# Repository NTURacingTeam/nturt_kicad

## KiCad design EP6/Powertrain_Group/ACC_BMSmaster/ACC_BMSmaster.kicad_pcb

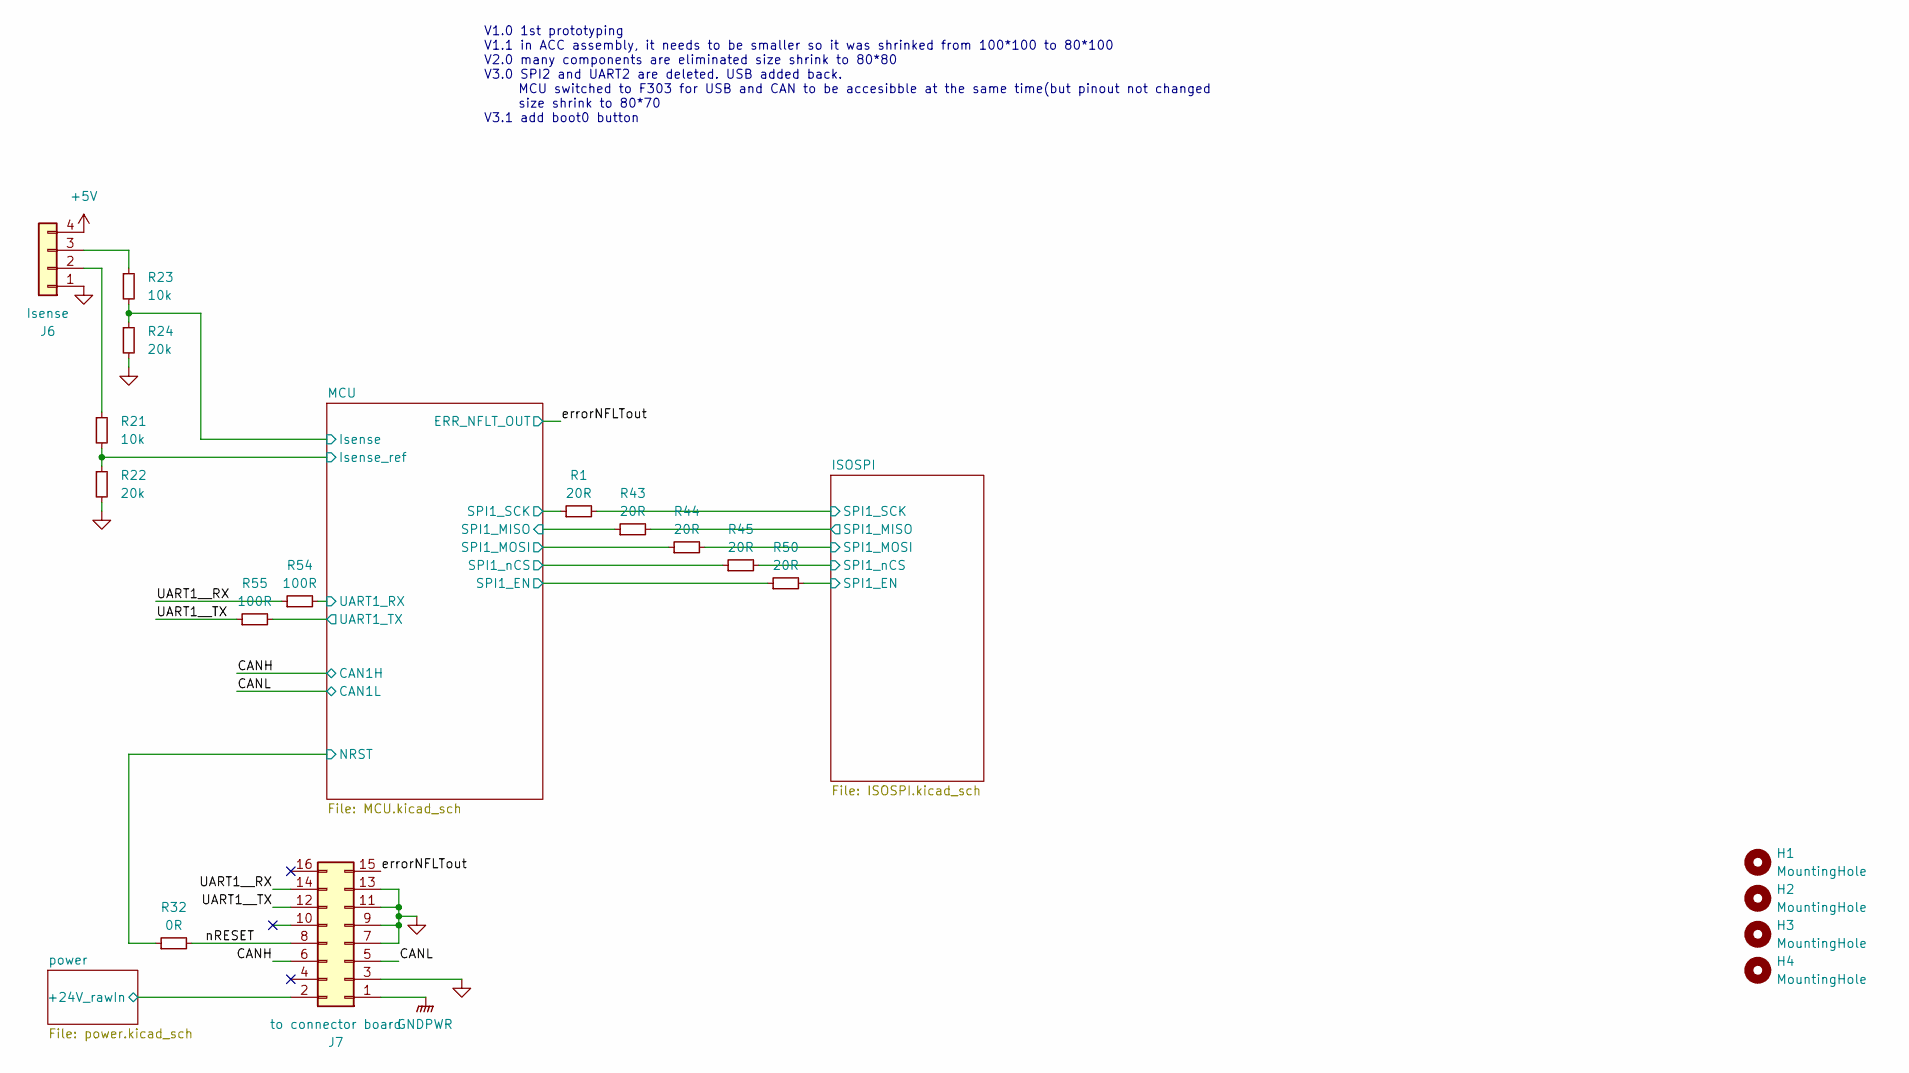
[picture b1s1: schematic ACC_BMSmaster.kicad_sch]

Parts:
H1, H2, H3, H4: MountingHole; MountingHole_3.2mm_M3
J6: Isense; JST_PH_B4B-PH-K_1x04_P2.00mm_Vertical
J7: to connector board; IDC-Header_2x08_P2.54mm_Vertical
R1, R43, R44, R45, R50: 20R; R_0402_1005Metric
R21, R23: 10k; R_0402_1005Metric
R22, R24: 20k; R_0402_1005Metric
R32: 0R; R_0402_1005Metric
R54, R55: 100R; R_0402_1005Metric

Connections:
+5V: J6.4; also elsewhere on the board
/CANH: J7.6; also elsewhere on the board
/CANL: J7.5; also elsewhere on the board
/ISOSPI/SPI1_EN: R50.2; also elsewhere on the board
/ISOSPI/SPI1_MISO: R43.2; also elsewhere on the board
/ISOSPI/SPI1_MOSI: R44.2; also elsewhere on the board
/ISOSPI/SPI1_SCK: R1.2; also elsewhere on the board
/ISOSPI/SPI1_nCS: R45.2; also elsewhere on the board
/MCU/Isense: R23.2, R24.1; also elsewhere on the board
/MCU/Isense_ref: R21.2, R22.1; also elsewhere on the board
/MCU/SPI1_EN: R50.1; also elsewhere on the board
/MCU/SPI1_MISO: R43.1; also elsewhere on the board
/MCU/SPI1_MOSI: R44.1; also elsewhere on the board
/MCU/SPI1_SCK: R1.1; also elsewhere on the board
/MCU/SPI1_nCS: R45.1; also elsewhere on the board
/MCU/SWD_NRST: R32.1; also elsewhere on the board
/MCU/UART1_RX: R54.2; also elsewhere on the board
/MCU/UART1_TX: R55.2; also elsewhere on the board
/UART1__RX: J7.14, R54.1
/UART1__TX: J7.12, R55.1
/errorNFLTout: J7.15; also elsewhere on the board
/nRESET: J7.8, R32.2
/power/+24V_preCMfilter: J7.2; also elsewhere on the board
GND: J6.1, J7.3, J7.7, J7.9, J7.11, J7.13, R22.2, R24.2; also elsewhere on the board
GNDPWR: J7.1; also elsewhere on the board
unnamed: J6.2, R21.1
unnamed: J6.3, R23.1

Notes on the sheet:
V1.0 1st prototyping V1.1 in ACC assembly, it needs to be smaller so it was shrinked from 100*100 to 80*100 V2.0 many components are eliminated size shrink to 80*80 V3.0 SPI2 and UART2 are deleted. USB added back. MCU switched to F303 for USB and CAN to be accesibble at the same time(but pinout not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

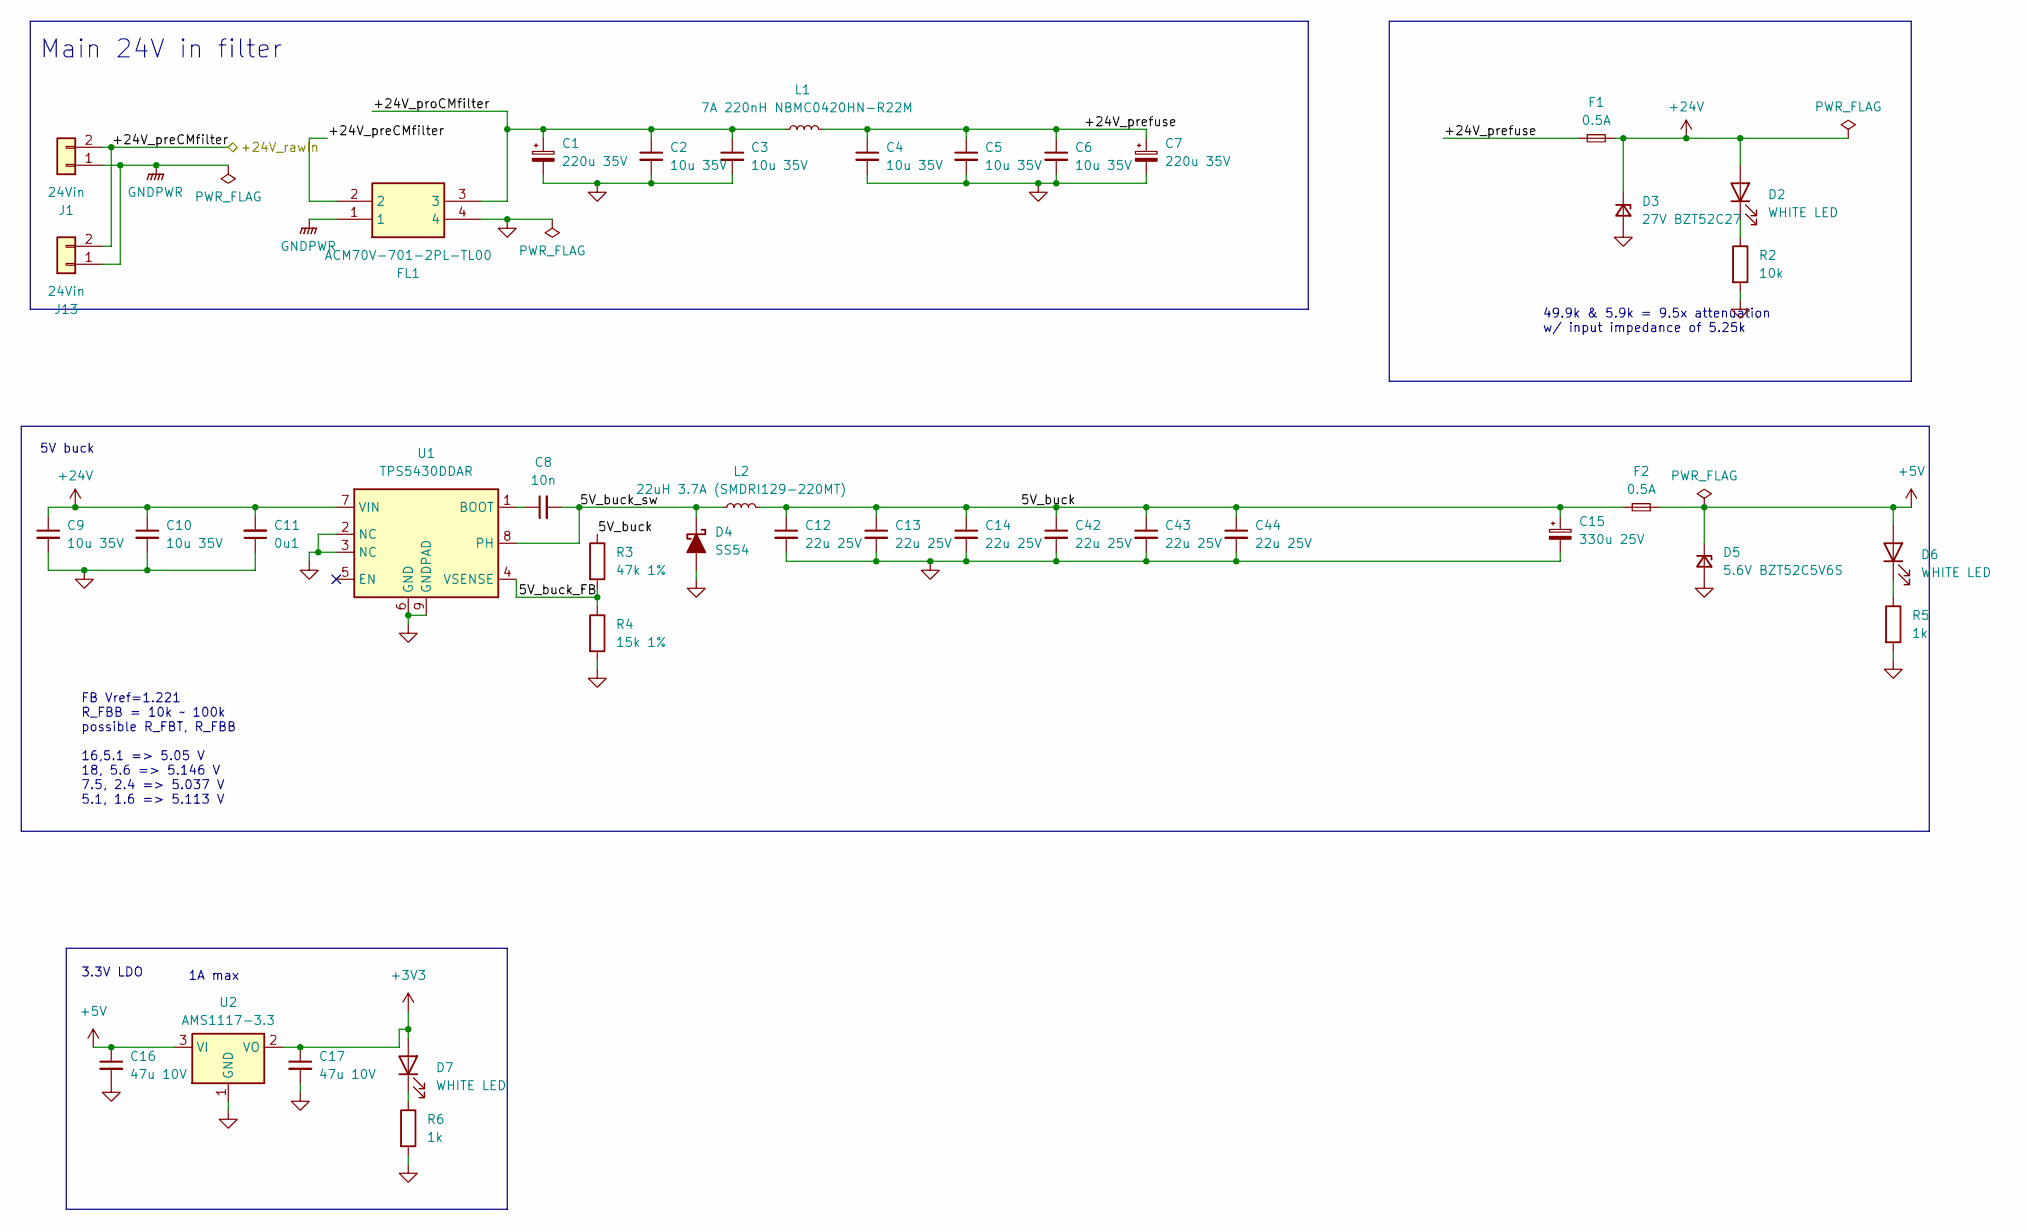
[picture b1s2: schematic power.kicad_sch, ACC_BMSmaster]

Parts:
C1, C7: 220u 35V; CP_Radial_D8.0mm_P3.80mm
C2, C3, C4, C5, C6, C9, C10: 10u 35V; C_1206_3216Metric
C8: 10n; C_0603_1608Metric
C11: 0u1; C_0603_1608Metric
C12, C13, C14, C42, C43, C44: 22u 25V; C_1206_3216Metric
C15: 330u 25V; CP_Radial_D8.0mm_P3.80mm
C16, C17: 47u 10V; C_1206_3216Metric
D2, D6, D7: WHITE LED; LED_0603_1608Metric
D3: 27V BZT52C27; D_SOD-323
D4: SS54; D_SMA
D5: 5.6V BZT52C5V6S; D_SOD-323
F1, F2: 0.5A; Fuse_1206_3216Metric
FL1: ACM70V-701-2PL-TL00; ACM70V7012PLTL00; Mouser Part Number 810-ACM70V7012PLTL00
J1, J13: 24Vin; JST_VH_B2P-VH_1x02_P3.96mm_Vertical
L1: 7A 220nH NBMC0420HN-R22M; L_Ferrocore_DLG-0403
L2: 22uH 3.7A (SMDRI129-220MT); L_Bourns_SRR1260
R2: 10k; R_0402_1005Metric
R3: 47k 1%; R_0603_1608Metric
R4: 15k 1%; R_0603_1608Metric
R5, R6: 1k; R_0402_1005Metric
U1: TPS5430DDAR; TI_SO-PowerPAD-8_ThermalVias
U2: AMS1117-3.3; SOT-223-3_TabPin2

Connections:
+3V3: C17.1, D7.2 (A), U2.2 (VO); also elsewhere on the board
+5V: C16.1, D5.1 (K), D6.2 (A), F2.2, U2.3 (VI); also elsewhere on the board
+24V: C9.1, C10.1, C11.2, D2.2 (A), D3.1 (K), F1.2, U1.7 (VIN)
/power/5V_buck: C12.1, C13.1, C14.1, C15.1, C42.1, C43.1, C44.1, F2.1, L2.2, R3.1
/power/5V_buck_FB: R3.2, R4.1, U1.4 (VSENSE)
/power/5V_buck_sw: C8.2, D4.1 (K), L2.1, U1.8 (PH)
/power/+24V_preCMfilter: FL1.2, J1.2, J13.2; also elsewhere on the board
/power/+24V_prefuse: C4.1, C5.1, C6.1, C7.1, F1.1, L1.2
/power/+24V_proCMfilter: C1.1, C2.1, C3.1, FL1.3, L1.1
GND: C1.2, C2.2, C3.2, C4.2, C5.2, C6.2, C7.2, C9.2, C10.2, C11.1, C12.2, C13.2, C14.2, C15.2, C16.2, C17.2, C42.2, C43.2, C44.2, D3.2 (A), D4.2 (A), D5.2 (A), FL1.4, R2.2, R4.2, R5.2, R6.2, U1.2 (NC), U1.3 (NC), U1.6 (GND), U1.9 (GNDPAD), U2.1 (GND); also elsewhere on the board
GNDPWR: FL1.1, J1.1, J13.1; also elsewhere on the board
unnamed: D2.1 (K), R2.1
unnamed: D6.1 (K), R5.1
unnamed: D7.1 (K), R6.1
unnamed: C8.1, U1.1 (BOOT)

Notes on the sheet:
49.9k & 5.9k = 9.5x attenuation w/ input impedance of 5.25k
FB Vref=1.221 R_FBB = 10k ~ 100k possible R_FBT, R_FBB 16,5.1 => 5.05 V 18, 5.6 => 5.146 V 7.5, 2.4 => 5.037 V 5.1, 1.6 => 5.113 V
1A max
5V buck
3.3V LDO
Main 24V in filter

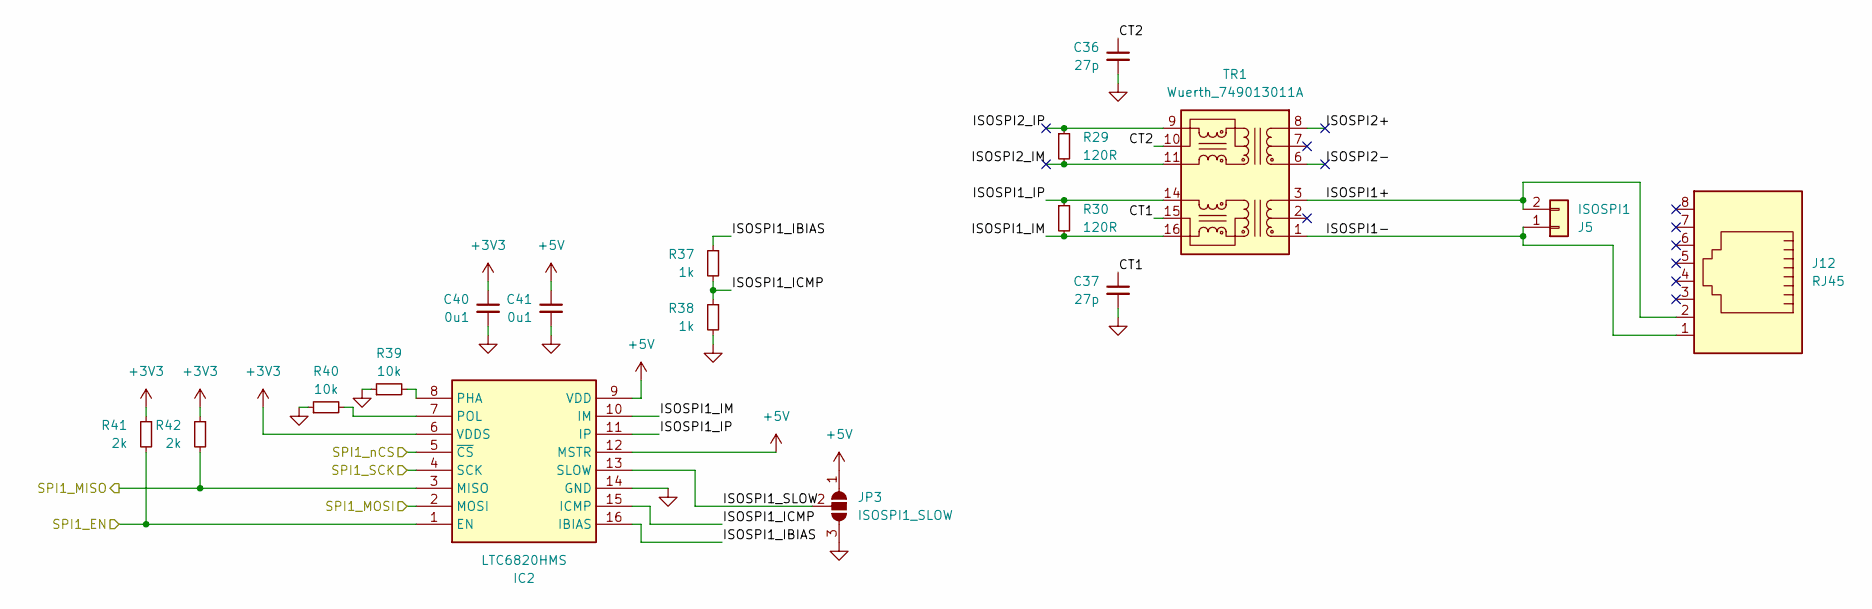
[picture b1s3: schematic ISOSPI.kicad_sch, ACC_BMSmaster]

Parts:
C36, C37: 27p; C_0402_1005Metric
C40, C41: 0u1; C_0402_1005Metric
IC2: LTC6820HMS; SOP50P490X110-16N; Mouser Part Number 584-LTC6820HMS#PBF
J5: ISOSPI1; JST_XH_B2B-XH-A_1x02_P2.50mm_Vertical
J12: RJ45; RJ45_Amphenol_54602-x08_Horizontal
JP3: ISOSPI1_SLOW; SolderJumper-3_P1.3mm_Open_RoundedPad1.0x1.5mm
R29, R30: 120R; R_0402_1005Metric
R37, R38: 1k; R_0402_1005Metric
R39, R40: 10k; R_0402_1005Metric
R41, R42: 2k; R_0402_1005Metric
TR1: Wuerth_749013011A; Transformer_Ethernet_Wuerth_749013011A

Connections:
+3V3: C40.1, IC2.6 (VDDS), R41.1, R42.1; also elsewhere on the board
+5V: C41.1, IC2.9 (VDD), IC2.12 (MSTR), JP3.1 (A); also elsewhere on the board
/ISOSPI/CT1: C37.1, TR1.15 (C_TX)
/ISOSPI/CT2: C36.1, TR1.10 (C_RX)
/ISOSPI/ISOSPI1+: J5.2, J12.2, TR1.3 (TD-)
/ISOSPI/ISOSPI1-: J5.1, J12.1, TR1.1 (TD+)
/ISOSPI/ISOSPI1_IBIAS: IC2.16 (IBIAS), R37.1
/ISOSPI/ISOSPI1_ICMP: IC2.15 (ICMP), R37.2, R38.1
/ISOSPI/ISOSPI1_IM: IC2.10 (IM), R30.2, TR1.16 (TX+)
/ISOSPI/ISOSPI1_IP: IC2.11 (IP), R30.1, TR1.14 (TX-)
/ISOSPI/ISOSPI1_SLOW: IC2.13 (SLOW), JP3.2 (C)
/ISOSPI/ISOSPI2+: TR1.8 (RD-)
/ISOSPI/ISOSPI2-: TR1.6 (RD+)
/ISOSPI/ISOSPI2_IM: R29.2, TR1.11 (RX+)
/ISOSPI/ISOSPI2_IP: R29.1, TR1.9 (RX-)
/ISOSPI/SPI1_EN: IC2.1 (EN), R41.2; also elsewhere on the board
/ISOSPI/SPI1_MISO: IC2.3 (MISO), R42.2; also elsewhere on the board
/ISOSPI/SPI1_MOSI: IC2.2 (MOSI); also elsewhere on the board
/ISOSPI/SPI1_SCK: IC2.4 (SCK); also elsewhere on the board
/ISOSPI/SPI1_nCS: IC2.5 (~CS); also elsewhere on the board
GND: C36.2, C37.2, C40.2, C41.2, IC2.14 (GND), JP3.3 (B), R38.2, R39.1, R40.1; also elsewhere on the board
unnamed: IC2.8 (PHA), R39.2
unnamed: IC2.7 (POL), R40.2

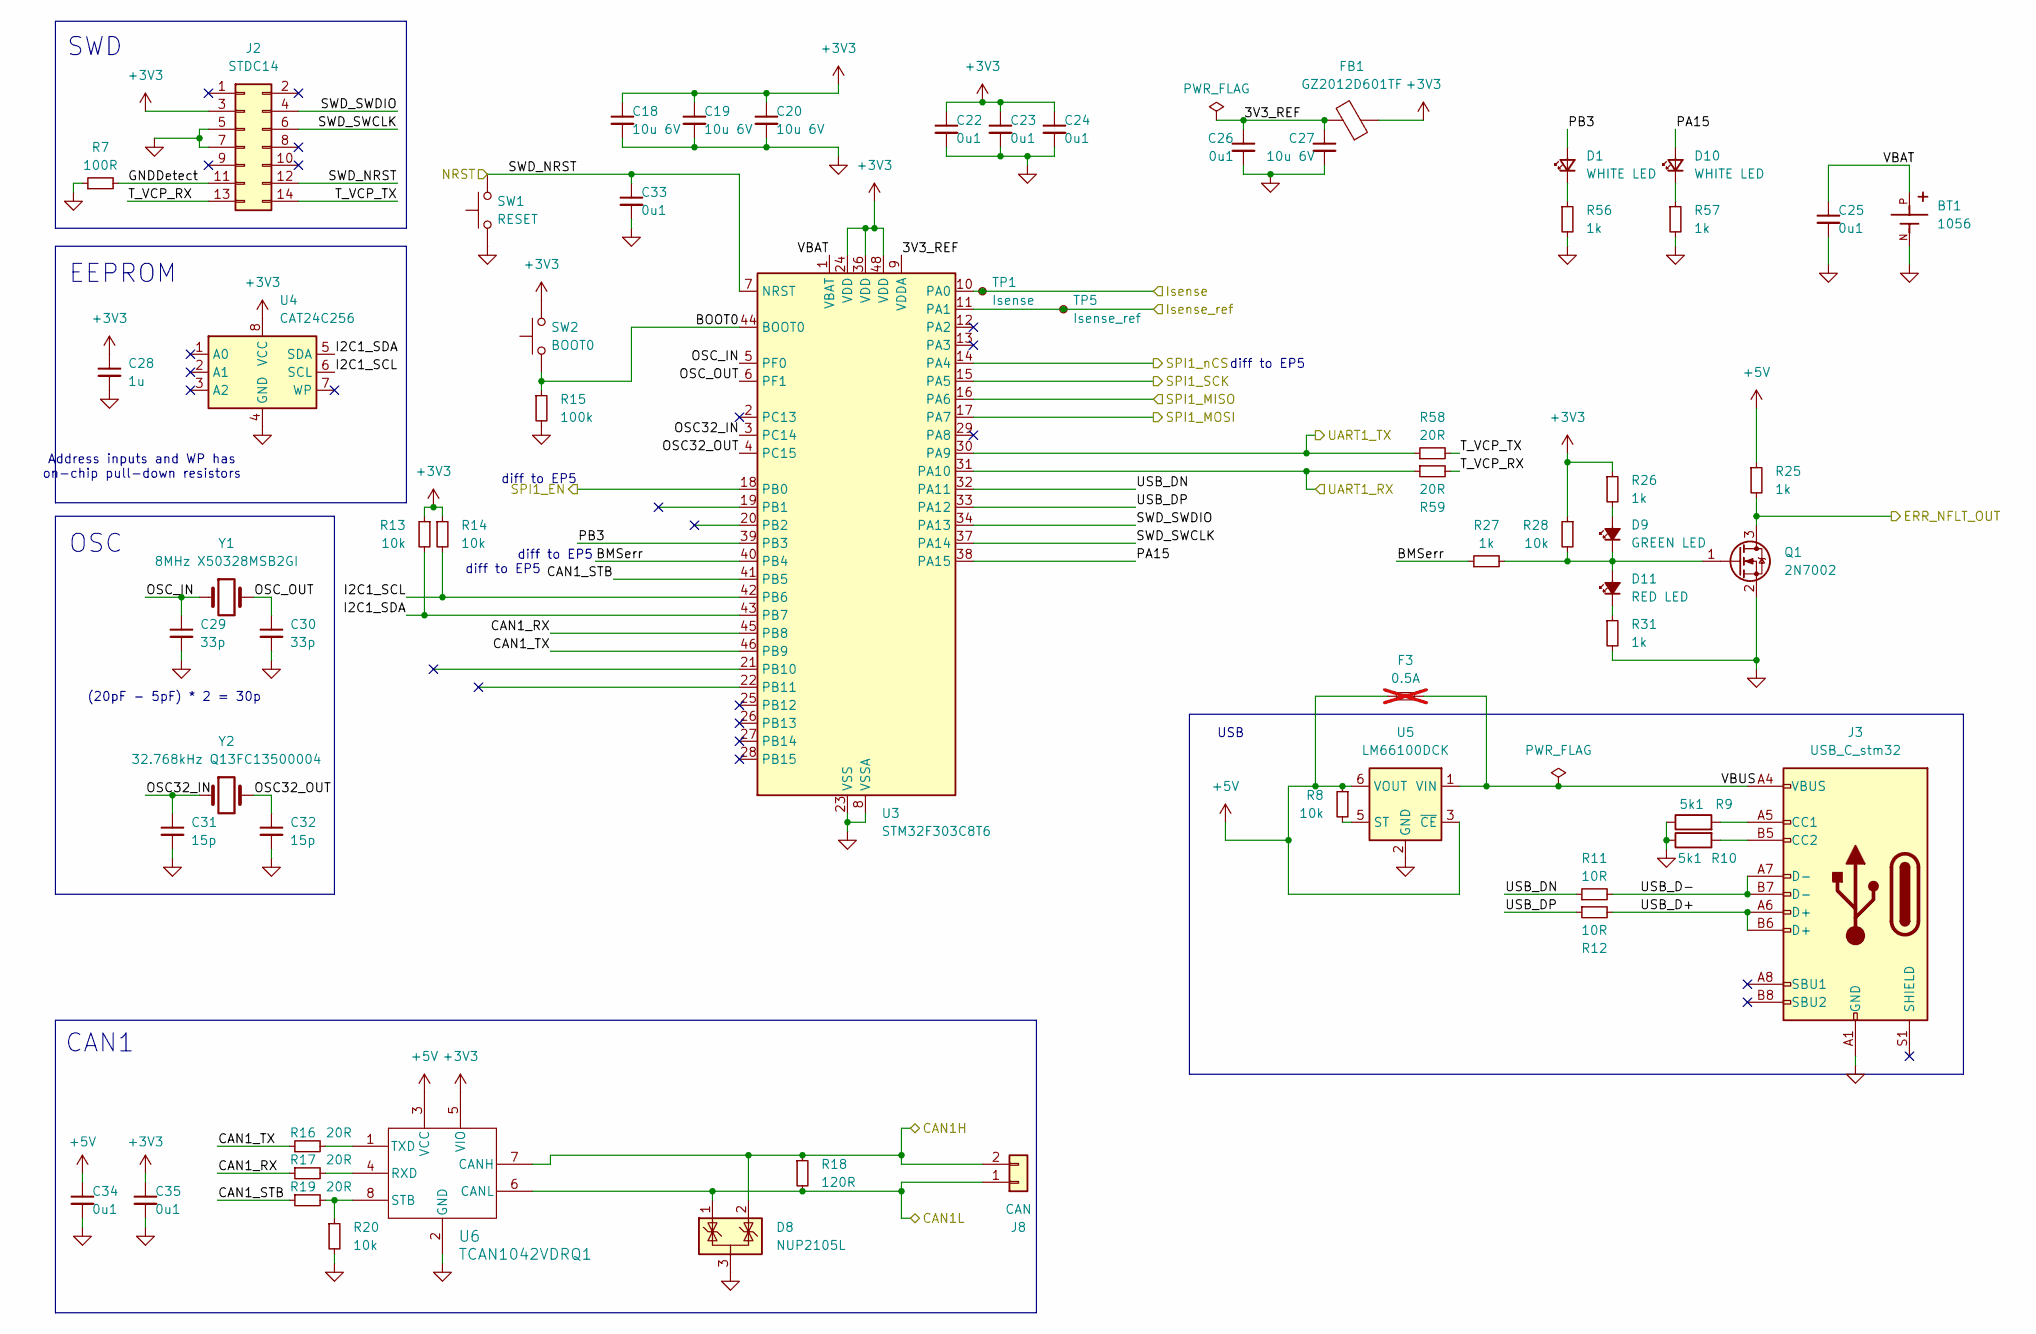
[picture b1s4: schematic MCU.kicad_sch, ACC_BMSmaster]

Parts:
BT1: 1056; BAT_1056; PARTREV D
C18, C19, C20, C27: 10u 6V; C_0402_1005Metric
C22, C23, C24, C25, C26, C33, C34, C35: 0u1; C_0402_1005Metric
C28: 1u; C_0402_1005Metric
C29, C30: 33p; C_0402_1005Metric
C31, C32: 15p; C_0402_1005Metric
D1, D10: WHITE LED; LED_0603_1608Metric
D8: NUP2105L; SOT-23
D9: GREEN LED; LED_0603_1608Metric
D11: RED LED; LED_0603_1608Metric
F3: 0.5A; Fuse_1206_3216Metric; not fitted
FB1: GZ2012D601TF; L_0805_2012Metric
J2: STDC14; box_header_14P_pitch127
J3: USB_C_stm32; USB_C_Receptacle_GCT_USB4105-xx-A_16P_TopMnt_Horizontal
J8: CAN; JST_XH_B2B-XH-A_1x02_P2.50mm_Vertical
Q1: 2N7002; SOT-23
R7: 100R; R_0402_1005Metric
R8, R13, R14, R20, R28: 10k; R_0402_1005Metric
R9, R10: 5k1; R_0402_1005Metric
R11, R12: 10R; R_0402_1005Metric
R15: 100k; R_0402_1005Metric
R16, R17, R19, R58, R59: 20R; R_0402_1005Metric
R18: 120R; R_0402_1005Metric
R25, R26, R27, R31, R56, R57: 1k; R_0402_1005Metric
SW1: RESET; SW_Tactile_SPST_NO_Straight_CK_PTS636Sx25SMTRLFS
SW2: BOOT0; SW_Tactile_SPST_NO_Straight_CK_PTS636Sx25SMTRLFS
TP1: Isense; TestPoint_Pad_D1.0mm
TP5: Isense_ref; TestPoint_Pad_D1.0mm
U3: STM32F303C8T6; LQFP-48_7x7mm_P0.5mm
U4: CAT24C256; SOIC-8_3.9x4.9mm_P1.27mm
U5: LM66100DCK; SOT-363_SC-70-6
U6: TCAN1042VDRQ1; SOIC-8_3.9x4.9mm_P1.27mm
Y1: 8MHz X50328MSB2GI; Crystal_SMD_5032-2Pin_5.0x3.2mm
Y2: 32.768kHz Q13FC13500004; Crystal_SMD_3215-2Pin_3.2x1.5mm

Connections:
+3V3: C18.1, C19.1, C20.1, C22.1, C23.1, C24.1, C28.1, C35.1, FB1.1, J2.3, R13.1, R14.1, R26.1, R28.1, SW2.2, U3.24 (VDD), U3.36 (VDD), U3.48 (VDD), U4.8 (VCC), U6.5 (VIO); also elsewhere on the board
+5V: C34.1, F3.1, R8.1, R25.1, U5.3 (~CE), U5.6 (VOUT), U6.3 (VCC); also elsewhere on the board
/CANH: D8.2 (K), J8.2, R18.1, U6.7 (CANH); also elsewhere on the board
/CANL: D8.1 (K), J8.1, R18.2, U6.6 (CANL); also elsewhere on the board
/MCU/3V3_REF: C26.1, C27.1, FB1.2, U3.9 (VDDA)
/MCU/BMSerr: R27.1, U3.40 (PB4)
/MCU/BOOT0: R15.1, SW2.1, U3.44 (BOOT0)
/MCU/CAN1_RX: R17.1, U3.45 (PB8)
/MCU/CAN1_STB: R19.1, U3.41 (PB5)
/MCU/CAN1_TX: R16.1, U3.46 (PB9)
/MCU/GNDDetect: J2.11, R7.2
/MCU/I2C1_SCL: R14.2, U3.42 (PB6), U4.6 (SCL)
/MCU/I2C1_SDA: R13.2, U3.43 (PB7), U4.5 (SDA)
/MCU/Isense: TP1.1, U3.10 (PA0); also elsewhere on the board
/MCU/Isense_ref: TP5.1, U3.11 (PA1); also elsewhere on the board
/MCU/OSC32_IN: C31.1, U3.3 (PC14), Y2.1
/MCU/OSC32_OUT: C32.1, U3.4 (PC15), Y2.2
/MCU/OSC_IN: C29.1, U3.5 (PF0), Y1.1
/MCU/OSC_OUT: C30.1, U3.6 (PF1), Y1.2
/MCU/PA15: D10.2 (A), U3.38 (PA15)
/MCU/PB3: D1.2 (A), U3.39 (PB3)
/MCU/SPI1_EN: U3.18 (PB0); also elsewhere on the board
/MCU/SPI1_MISO: U3.16 (PA6); also elsewhere on the board
/MCU/SPI1_MOSI: U3.17 (PA7); also elsewhere on the board
/MCU/SPI1_SCK: U3.15 (PA5); also elsewhere on the board
/MCU/SPI1_nCS: U3.14 (PA4); also elsewhere on the board
/MCU/SWD_NRST: C33.1, J2.12, SW1.2, U3.7 (NRST); also elsewhere on the board
/MCU/SWD_SWCLK: J2.6, U3.37 (PA14)
/MCU/SWD_SWDIO: J2.4, U3.34 (PA13)
/MCU/T_VCP_RX: J2.13, R59.2
/MCU/T_VCP_TX: J2.14, R58.2
/MCU/UART1_RX: R59.1, U3.31 (PA10); also elsewhere on the board
/MCU/UART1_TX: R58.1, U3.30 (PA9); also elsewhere on the board
/MCU/USB_D+: J3.A6 (D+), J3.B6 (D+), R12.2
/MCU/USB_D-: J3.A7 (D-), J3.B7 (D-), R11.2
/MCU/USB_DN: R11.1, U3.32 (PA11)
/MCU/USB_DP: R12.1, U3.33 (PA12)
/MCU/VBAT: BT1.P, C25.1, U3.1 (VBAT)
/MCU/VBUS: F3.2, J3.A4 (VBUS), J3.A9 (VBUS), J3.B4 (VBUS), J3.B9 (VBUS), U5.1 (VIN)
/errorNFLTout: Q1.3 (D), R25.2; also elsewhere on the board
GND: BT1.N, C18.2, C19.2, C20.2, C22.2, C23.2, C24.2, C25.2, C26.2, C27.2, C28.2, C29.2, C30.2, C31.2, C32.2, C33.2, C34.2, C35.2, D8.3 (A), J2.5, J2.7, J3.A1 (GND), J3.A12 (GND), J3.B1 (GND), J3.B12 (GND), Q1.2 (S), R7.1, R9.1, R10.1, R15.2, R20.2, R31.2, R56.2, R57.2, SW1.1, U3.8 (VSSA), U3.23 (VSS), U3.35 (VSS), U3.47 (VSS), U4.4 (GND), U5.2 (GND), U6.2 (GND); also elsewhere on the board
unnamed: D1.1 (K), R56.1
unnamed: D9.2 (A), R26.2
unnamed: D10.1 (K), R57.1
unnamed: D9.1 (K), D11.2 (A), Q1.1 (G), R27.2, R28.2
unnamed: D11.1 (K), R31.1
unnamed: J3.A5 (CC1), R9.2
unnamed: J3.B5 (CC2), R10.2
unnamed: R8.2, U5.5 (ST)
unnamed: R17.2, U6.4 (RXD)
unnamed: R19.2, R20.1, U6.8 (STB)
unnamed: R16.2, U6.1 (TXD)

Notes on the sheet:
diff to EP5
EEPROM
SWD
Address inputs and WP has on-chip pull-down resistors
OSC
(20pF - 5pF) * 2 = 30p
USB
CAN1

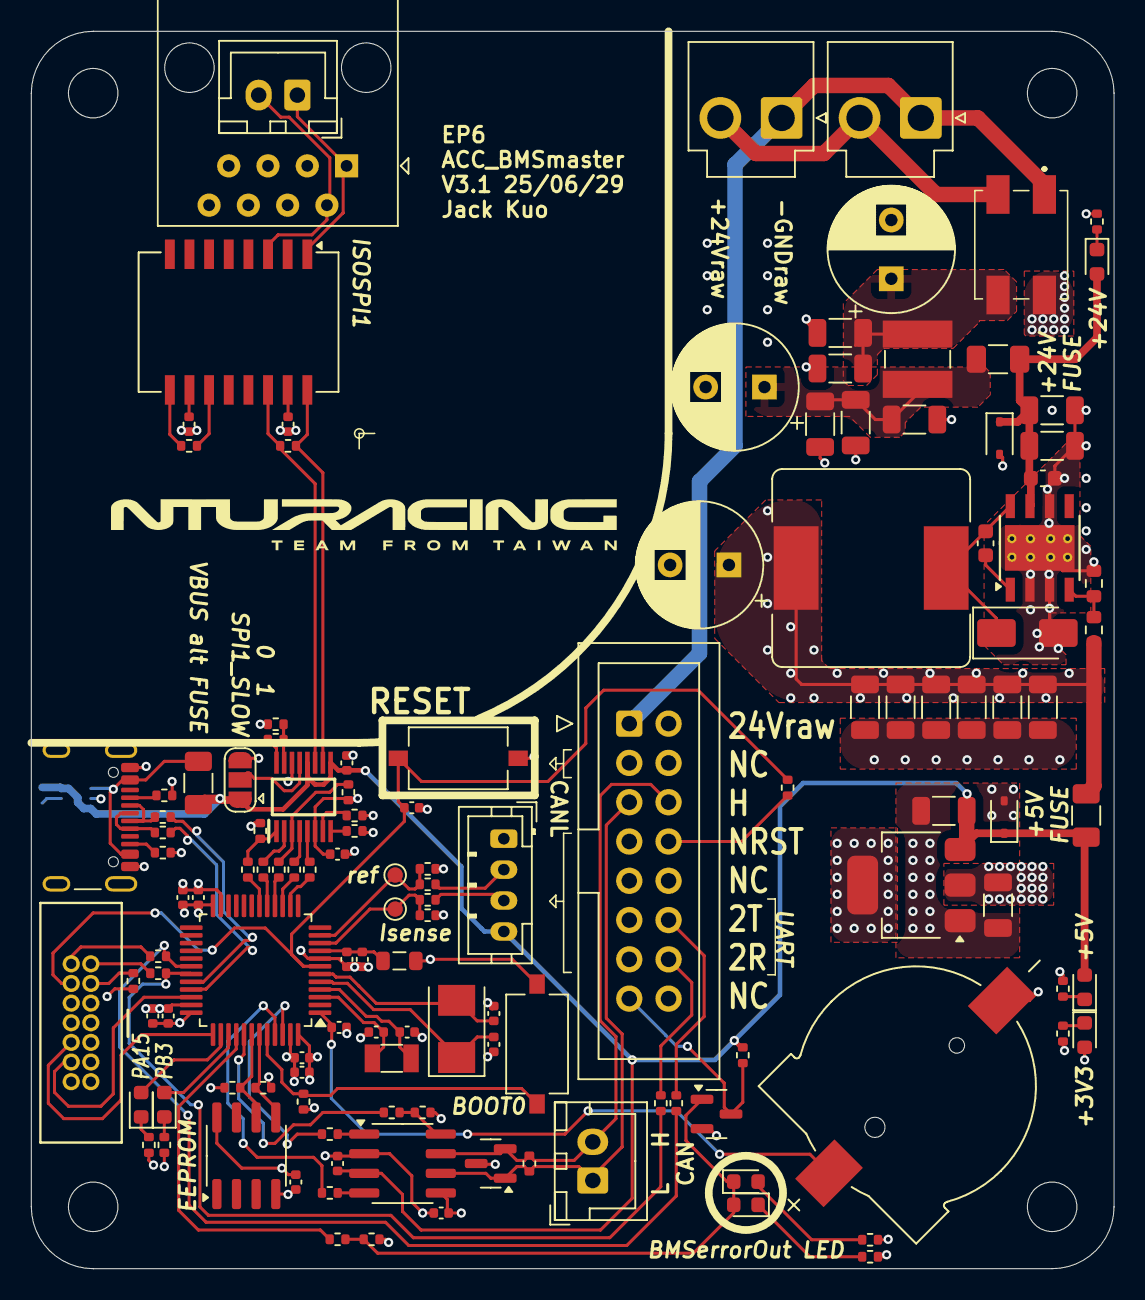
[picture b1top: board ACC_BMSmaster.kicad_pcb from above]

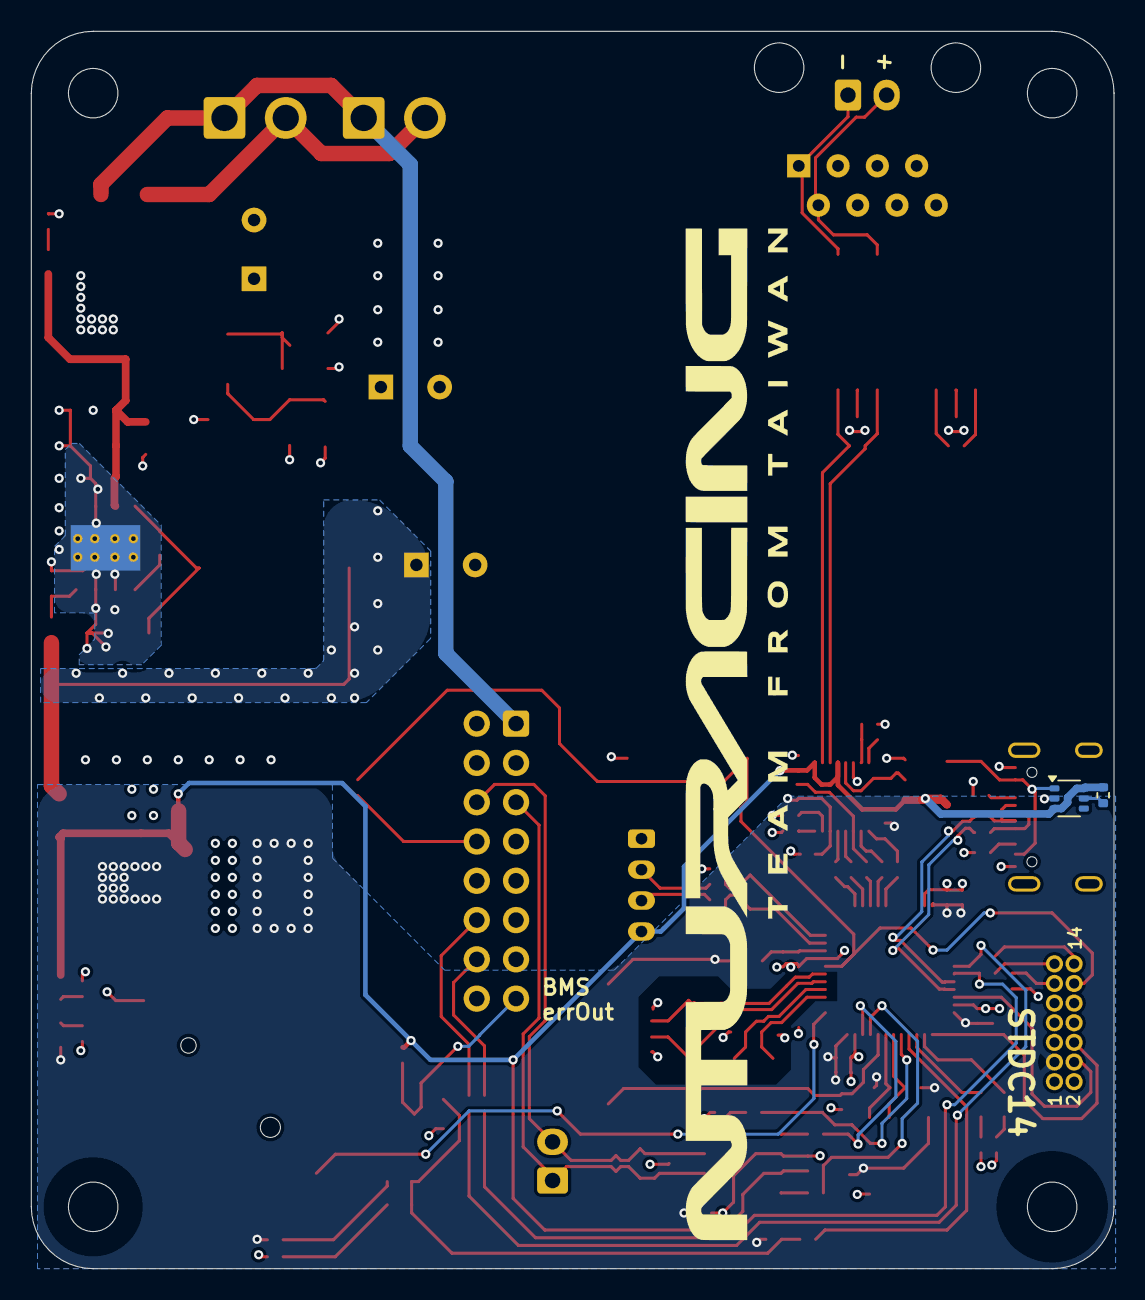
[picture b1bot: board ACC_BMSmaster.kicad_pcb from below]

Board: 4 copper layers, 70.0 x 80.0 mm, 137 parts (2 on the bottom side), 87 nets.
